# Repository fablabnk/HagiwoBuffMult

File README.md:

https://note.com/solder_state/n/n54e016f19c94#8e5c9ae0-af24-4910-aa9b-f91eed0dcada

- choosing to ignore issue that pads are too close to board edge by 0.03mm
- In future revision could add two 100n decoupling caps such as in [this design](https://www.skullandcircuits.com/utilities-buffered-multiple/?v=d3dcf429c679). Tried to add later on but it was too tight a squeeze.

# Build Instructions

S stands for socket
P stands for pin

# TODO

- check that two boards overlap

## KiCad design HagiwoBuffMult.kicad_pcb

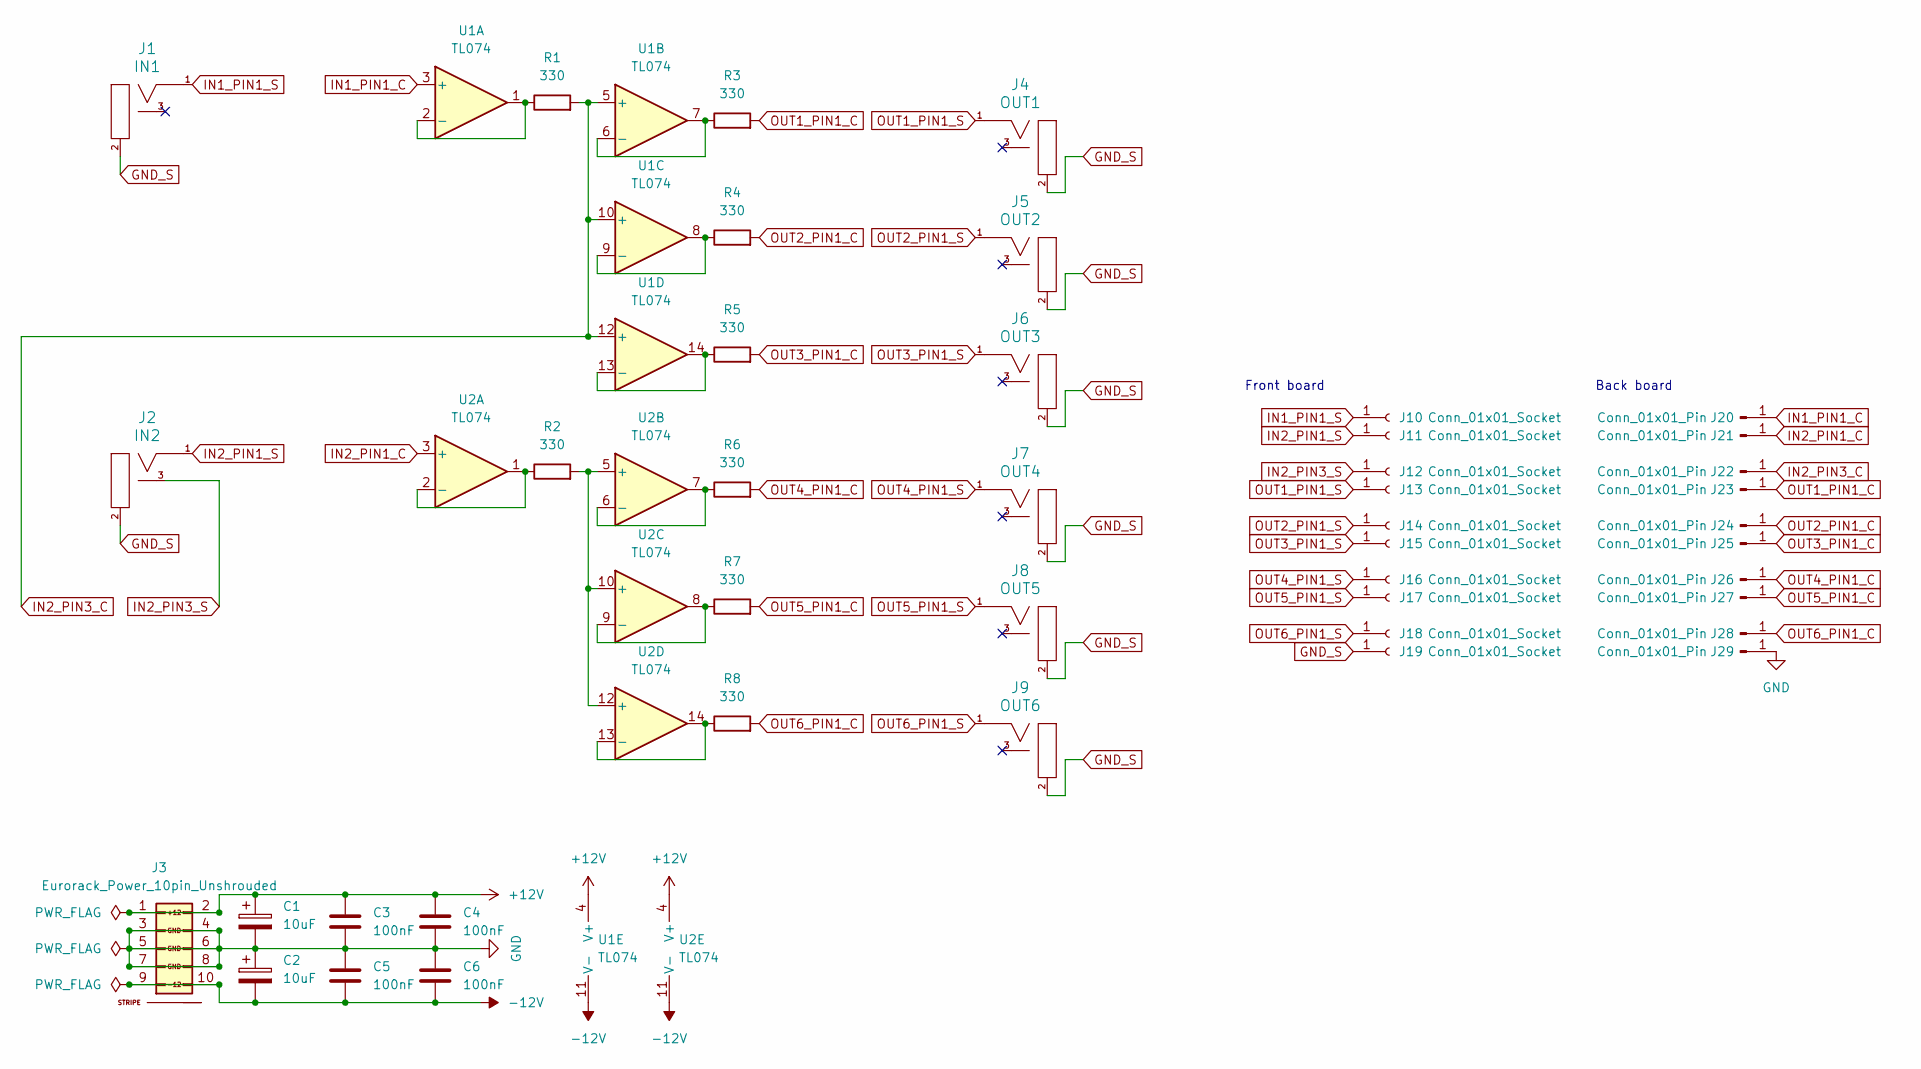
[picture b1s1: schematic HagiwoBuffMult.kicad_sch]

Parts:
C1, C2: 10uF; CP_Radial_D4.0mm_P2.00mm
C3, C4, C5, C6: 100nF; C_Disc_D3.0mm_W1.6mm_P2.50mm
J1: IN1; EighthInch_PJ398SM_3mmNPTH; Part Number WQP-WQP518MA
J2: IN2; EighthInch_PJ398SM_3mmNPTH; Part Number WQP-WQP518MA
J3: Eurorack_Power_10pin_Unshrouded; IDC-Header_2x05_P2.54mm_Vertical_Euro_Power_Striped_Thicker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; Part Number 1-1002FBV0T
J4: OUT1; EighthInch_PJ398SM_3mmNPTH; Part Number WQP-WQP518MA
J5: OUT2; EighthInch_PJ398SM_3mmNPTH; Part Number WQP-WQP518MA
J6: OUT3; EighthInch_PJ398SM_3mmNPTH; Part Number WQP-WQP518MA
J7: OUT4; EighthInch_PJ398SM_3mmNPTH; Part Number WQP-WQP518MA
J8: OUT5; EighthInch_PJ398SM_3mmNPTH; Part Number WQP-WQP518MA
J9: OUT6; EighthInch_PJ398SM_3mmNPTH; Part Number WQP-WQP518MA
J10, J11, J12, J13, J14, J15, J16, J17, J18, J19: Conn_01x01_Socket; PinSocket_1x01_P2.54mm_Vertical
J20, J21, J22, J23, J24, J25, J26, J27, J28, J29: Conn_01x01_Pin; PinHeader_1x01_P2.54mm_Vertical
R1, R2, R3, R4, R5, R6, R7, R8: 330; R_Axial_DIN0204_L3.6mm_D1.6mm_P1.90mm_Vertical
U1, U2: TL074; DIP-14_W7.62mm_Socket

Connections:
+12V: C1.1, C3.1, C4.1, J3.1 (+12V), J3.2 (+12V), U1.4 (V+), U2.4 (V+)
-12V: C2.2, C5.2, C6.2, J3.9 (-12V), J3.10 (-12V), U1.11 (V-), U2.11 (V-)
GND: C1.2, C2.1, C3.2, C4.2, C5.1, C6.1, J3.3 (GND), J3.4 (GND), J3.5 (GND), J3.6 (GND), J3.7 (GND), J3.8 (GND), J29.1
GND_S: J1.2 (SHEILD), J2.2 (SHEILD), J4.2 (SHEILD), J5.2 (SHEILD), J6.2 (SHEILD), J7.2 (SHEILD), J8.2 (SHEILD), J9.2 (SHEILD), J19.1
IN1_PIN1_C: J20.1, U1.3 (+)
IN1_PIN1_S: J1.1 (SIG), J10.1
IN2_PIN1_C: J21.1, U2.3 (+)
IN2_PIN1_S: J2.1 (SIG), J11.1
IN2_PIN3_C: J22.1, R1.2, U1.5 (+), U1.10 (+), U1.12 (+)
IN2_PIN3_S: J2.3 (SW), J12.1
unnamed: R1.1, U1.1, U1.2 (-)
unnamed: R3.1, U1.6 (-), U1.7
unnamed: R4.1, U1.8, U1.9 (-)
unnamed: R5.1, U1.13 (-), U1.14
unnamed: R2.1, U2.1, U2.2 (-)
unnamed: R2.2, U2.5 (+), U2.10 (+), U2.12 (+)
unnamed: R6.1, U2.6 (-), U2.7
unnamed: R7.1, U2.8, U2.9 (-)
unnamed: R8.1, U2.13 (-), U2.14
OUT1_PIN1_C: J23.1, R3.2
OUT1_PIN1_S: J4.1 (SIG), J13.1
OUT2_PIN1_C: J24.1, R4.2
OUT2_PIN1_S: J5.1 (SIG), J14.1
OUT3_PIN1_C: J25.1, R5.2
OUT3_PIN1_S: J6.1 (SIG), J15.1
OUT4_PIN1_C: J26.1, R6.2
OUT4_PIN1_S: J7.1 (SIG), J16.1
OUT5_PIN1_C: J27.1, R7.2
OUT5_PIN1_S: J8.1 (SIG), J17.1
OUT6_PIN1_C: J28.1, R8.2
OUT6_PIN1_S: J9.1 (SIG), J18.1

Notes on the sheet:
Back board
Front board

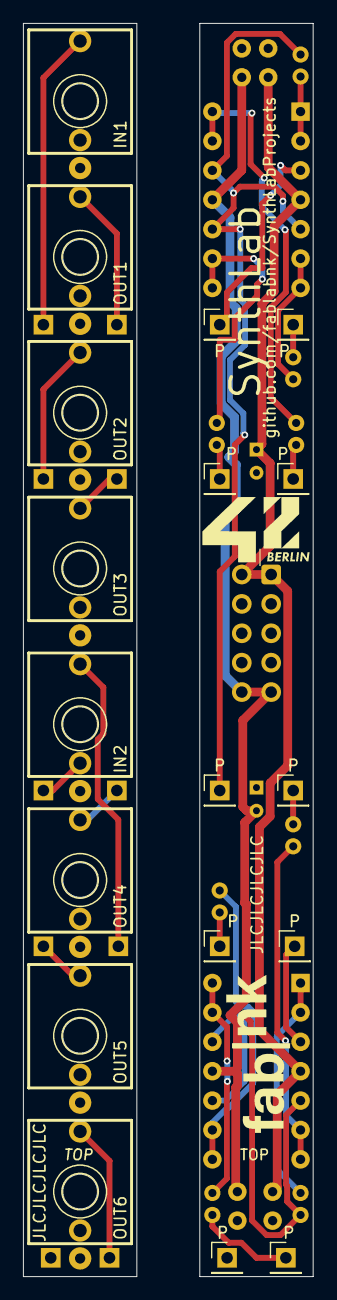
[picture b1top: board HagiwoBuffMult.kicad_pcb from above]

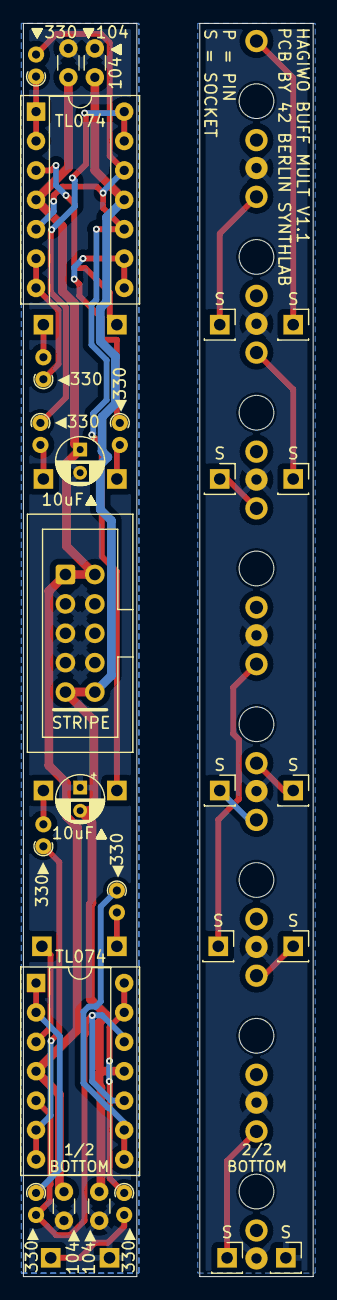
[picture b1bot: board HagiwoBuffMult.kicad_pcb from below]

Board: 2 copper layers, 25.0 x 108.3 mm, 45 parts (27 on the bottom side), 31 nets.

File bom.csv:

Reference,Value,Have It?,Datasheet,Footprint,Qty,DNP
"C1,C2",100n,104,~,Capacitor_THT:CP_Radial_D5.0mm_P2.50mm,2,
"IN1,IN2,OUT1,OUT2,OUT3,OUT4,OUT5,OUT6",3.5mm_Mono_Switched_sm,Y,,PCM_4ms_Jack:EighthInch_PJ398SM,8,
"J6,J7,J8,J10,J11,J12,J13,J14,J15,J16",Conn_01x01_Pin,Y,~,Connector_PinHeader_2.54mm:PinHeader_1x01_P2.54mm_Vertical,10,
J9,Eurorack_Power_10pin_Unshrouded,Y but order more from Ali,,Library:IDC-Header_2x05_P2.54mm_Vertical_Euro_Power_Striped,1,
"J17,J18,J19,J20,J21,J22,J23,J24,J25,J26",Conn_01x01_Socket,Y,~,Connector_PinSocket_2.54mm:PinSocket_1x01_P2.54mm_Vertical,10,
"R1,R2,R3,R4,R5,R6,R7,R8",330,Y,~,Resistor_THT:R_Axial_DIN0207_L6.3mm_D2.5mm_P7.62mm_Horizontal,8,
"U1,U2",TL074,Y but order more from Ali,http://www.ti.com/lit/ds/symlink/tl071.pdf,Package_DIP:DIP-14_W7.62mm_Socket,2,

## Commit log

2024-07-29 addition of 100n decoupling cap causing complications
2024-07-29 routed and made panel
2024-08-04 broke panel out into separate file and made board and panel width narrower in accordance with doefper A100 standard
2024-08-04 added branding and instructions
2024-08-11 v1.0 ready for production
2024-08-15 removed files for separate boards as in the end we will combine with other boards for production
2024-09-15 working on v1.1 - added build notes - widened 10uF cap footprint - what to do about traces being too close to board edge?
2024-09-15 Updated build notes
2024-09-22 v1.1 reaady for final check
2024-09-25 v1.1 checked
2024-12-01 updating after Dmitri's changes
